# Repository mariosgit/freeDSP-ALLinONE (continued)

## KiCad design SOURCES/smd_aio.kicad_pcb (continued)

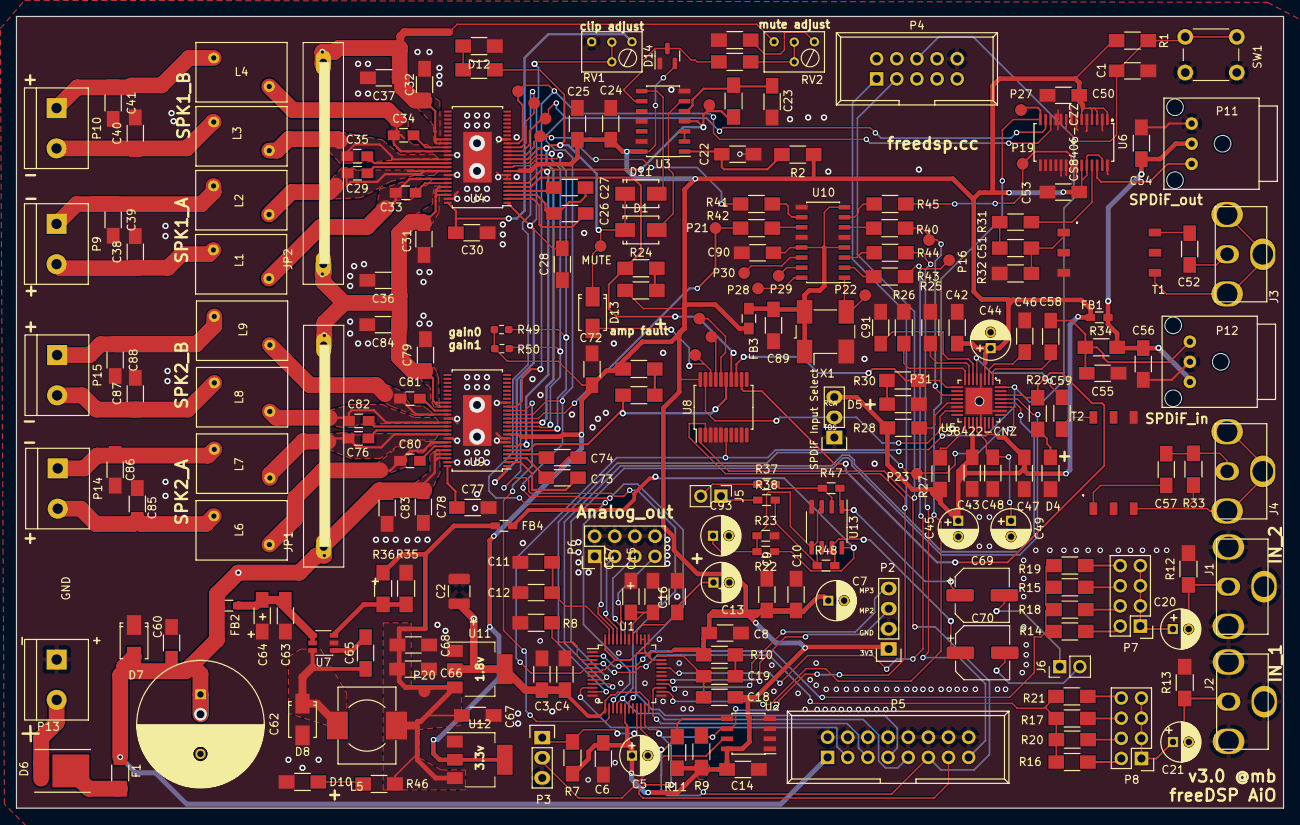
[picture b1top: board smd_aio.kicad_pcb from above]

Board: 2 copper layers, 159.8 x 99.8 mm, 228 parts (0 on the bottom side), 162 nets.

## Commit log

2024-01-24 Converted to KiCad7
2024-01-24 DRC checked.
2024-01-24 A bit more DRC checking.
2024-01-24 Removed redundant 7414 and pot, rerouted a bit.
2024-01-25 Removed ArduinoPort, Changed Power Supply. Rerouting and stuff.
2024-01-26 Added power down detection.
2024-01-29 Moved input cap and Reset btn.
2024-01-30 Added mute adjust, improved layout.
2024-01-31 Removed old files.
2024-01-31 Optimized Vreg traces.
2024-03-27 Added HP amp
2024-03-31 Added BAT54s OV protect.
2024-08-24 Cleaned up ground plane under amps.
2024-09-02 Fixed Vin/Vcc issue.
2024-09-03 Improved power traces.
2024-09-04 ideas...
2024-09-10 Minor improvents
2024-09-10 Made some space for under side heat sink.. todo, move the WP jumper.
